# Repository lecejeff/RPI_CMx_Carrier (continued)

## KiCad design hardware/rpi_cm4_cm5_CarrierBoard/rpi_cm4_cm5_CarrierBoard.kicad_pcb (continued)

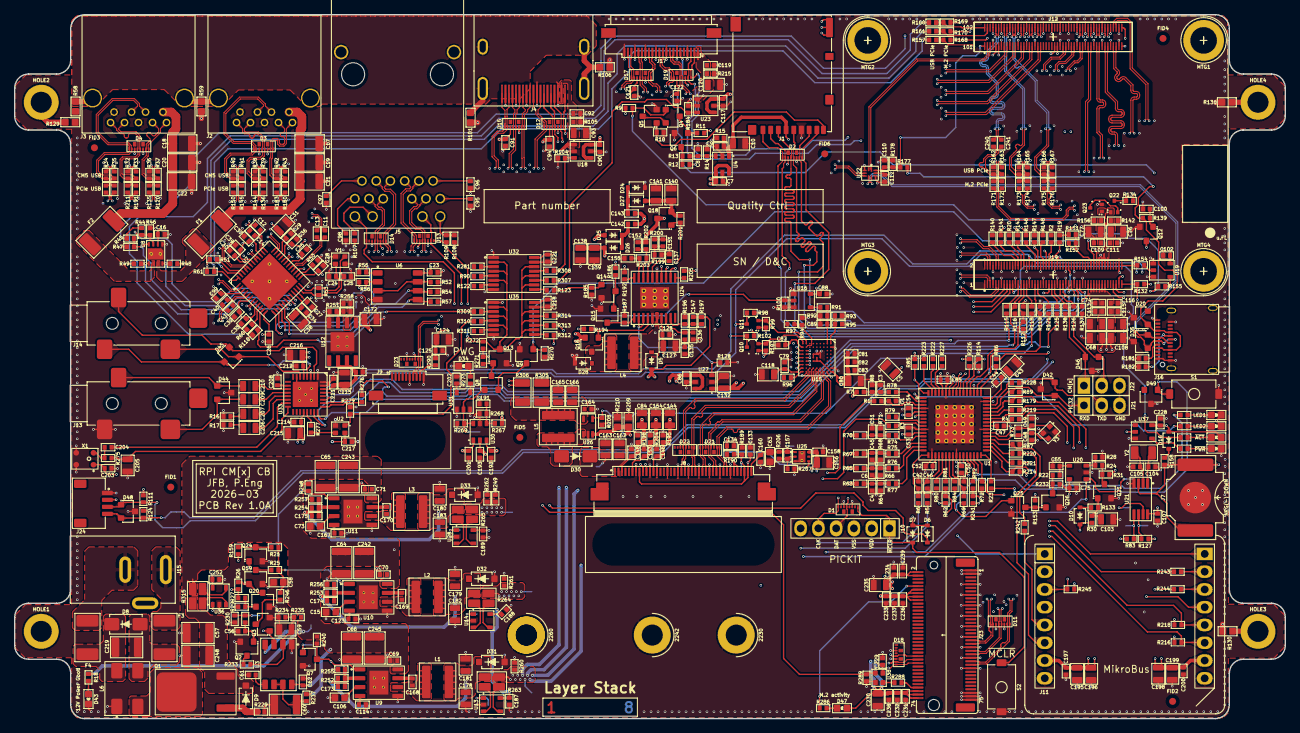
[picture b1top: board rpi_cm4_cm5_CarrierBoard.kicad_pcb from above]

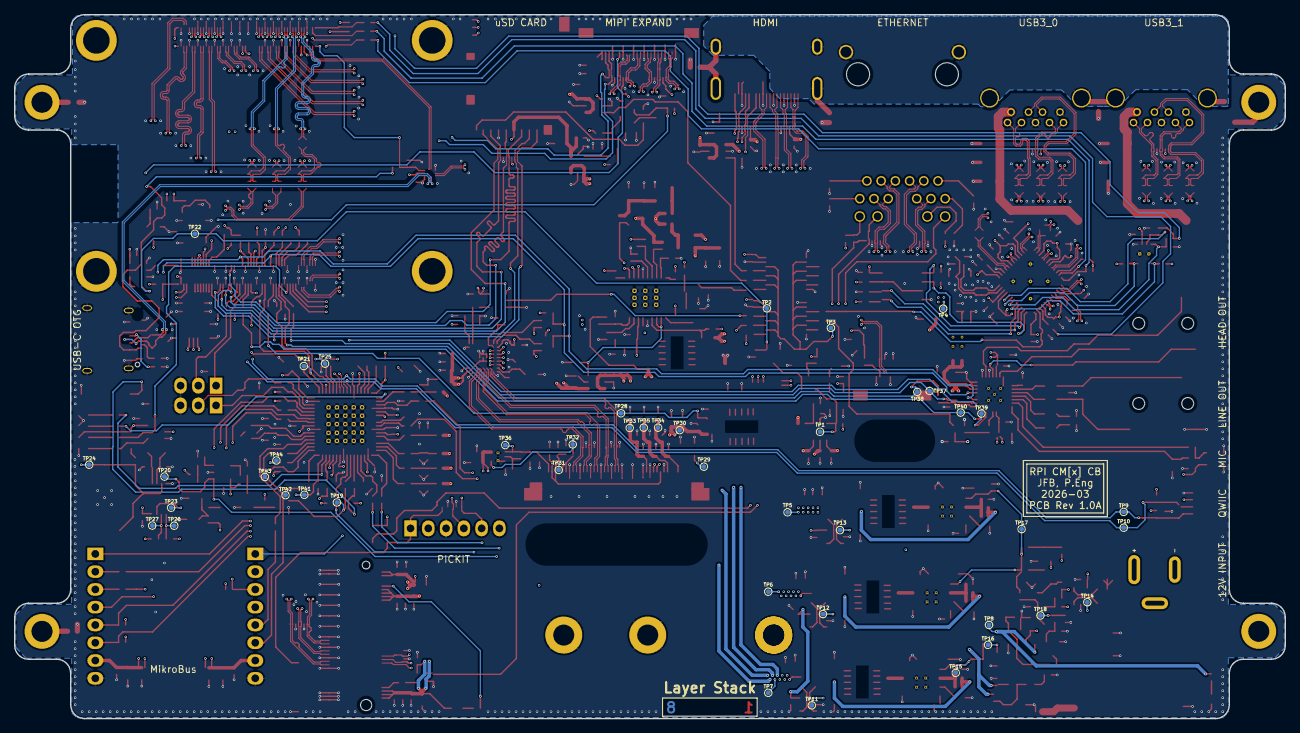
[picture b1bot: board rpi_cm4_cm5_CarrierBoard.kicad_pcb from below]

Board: 8 copper layers, 181.6 x 100.6 mm, 710 parts (45 on the bottom side), 449 nets.

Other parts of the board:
MTG**: Untitled; SLOT_TH_20_5mm
MTG**#2: Untitled; SLOT_TH_5_5mm

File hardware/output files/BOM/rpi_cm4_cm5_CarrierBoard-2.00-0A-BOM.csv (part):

"Reference","Qty","Value","Description","DNP","Exclude from BOM","Exclude from Board","Manufacturer","Manufacturer Part Number","Distributor","Distributor Part Number","Footprint","Datasheet"
"C1,C7,C9,C11,C12,C13,C14,C16,C23,C26,C27,C28,C29,C30,C32,C33,C34,C35,C36,C37,C39,C40,C41,C42,C44,C46,C47,C50,C52,C53,C54,C55,C56,C62,C69,C70,C71,C72,C74,C75,C79,C81,C82,C83,C85,C86,C87,C88,C90,C91,C92,C94,C95,C96,C97,C98,C99,C100,C102,C107,C109,C110,C111,C112,C113,C115,C116,C117,C119,C121,C122,C125,C128,C133,C134,C142,C143,C146,C148,C153,C155,C158,C160,C164,C168,C169,C170,C187,C188,C189,C197,C200,C202,C203,C204,C208,C211,C212,C214,C217,C218,C221,C228,C229,C231,C232,C233,C234,C236,C237,C238,C239,C240,C241,C252,C253","116","0.1u","CAP CER 0.1UF 50V X7R 0402","","","","Murata Electronics","GRM155R71H104KE14D","DigiKey","490-10700-1-ND","footprint:CAP_NONPOL_0402","https://search.murata.co.jp/Ceramy/image/img/A01X/G101/ENG/G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"
"C3,C4,C6,C45,C51,C191,C192,C193,C201","9","1n","CAP CER 1000PF 50V C0G/NP0 0402","","","","Murata Electronics","GRM1555C1H102JA01D","DigiKey","490-3244-1-ND","footprint:CAP_NONPOL_0402","https://search.murata.co.jp/Ceramy/image/img/A01X/G101/ENG/G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"
"C5,C10,C31,C38,C43,C67,C68,C76,C77,C78,C80,C93,C108,C118,C120,C127,C132,C144,C154,C156,C162,C163,C165,C166,C172,C178,C179,C180,C181,C182,C183,C230,C235","33","22u","CAP CER 22UF 25V X5R 0805","","","","Samsung Electro-Mechanics","CL21A226MAYNNNE","DigiKey","1276-CL21A226MAYNNNECT-ND","footprint:CAP_NONPOL_0805","https://mm.digikey.com/Volume0/opasdata/d220001/medias/docus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"
"C8","1","0.1u","CAP CER 0.1UF 50V X7R 0402","DNP","","","Murata Electronics","GRM155R71H104KE14D","DigiKey","490-10700-1-ND","footprint:CAP_NONPOL_0402","https://search.murata.co.jp/Ceramy/image/img/A01X/G101/ENG/G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"
"C15,C58,C63,C73,C106","5","1u","CAP CER 1UF 16V X7R 0603","","","","YAGEO","CC0603KRX7R7BB105","DigiKey","311-1446-1-ND","footprint:CAP_NONPOL_0603","https://www.yageogroup.com/content/datasheet/asset/file/UPY-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"
"C17,C18,C19,C20,C21,C22","6","47u","CAP CER 47UF 16V X5R 1206","","","","TDK Corporation","C3216X5R1C476M160AB","DigiKey","445-6003-1-ND","footprint:CAP_NONPOL_1206","https://product.tdk.com/system/files/dam/doc/product/capacit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"
"C24,C25,C48,C49","4","13p","CAP CER 13PF 50V C0G/NP0 0402","","","","Murata Electronics","GJM1555C1H130GB01D","DigiKey","490-8079-1-ND","footprint:CAP_NONPOL_0402","https://search.murata.co.jp/Ceramy/image/img/A01X/G101/ENG/G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"
"C57,C60,C64,C65,C66,C219,C242,C243,C245,C248","10","10u","CAP CER 10UF 50V X7R 1210","","","","TDK Corporation","C3225X7R1H106K250AC","DigiKey","445-C3225X7R1H106K250ACCT-ND","footprint:CAP_NONPOL_1210","https://product.tdk.com/system/files/dam/doc/product/capacit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"
"C59,C84,C103,C124,C138,C139,C140,C141,C195,C199,C206,C207,C209,C210,C213,C215","16","1u","CAP CER 1UF 50V X7R 0805","","","","YAGEO","CC0805KKX7R9BB105","DigiKey","311-1886-1-ND","footprint:CAP_NONPOL_0805","https://www.yageogroup.com/content/datasheet/asset/file/UPY-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"
"C61,C114,C123,C167","4","10n","CAP CER 10000PF 50V X7R 0402","","","","Murata Electronics","GCM155R71H103KA55D","DigiKey","490-4762-1-ND","footprint:CAP_NONPOL_0402","https://search.murata.co.jp/Ceramy/image/img/A01X/G101/ENG/G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"
"C89","1","1n","CAP CER 1000PF 50V C0G/NP0 0402","DNP","","","Murata Electronics","GRM1555C1H102JA01D","DigiKey","490-3244-1-ND","footprint:CAP_NONPOL_0402","https://search.murata.co.jp/Ceramy/image/img/A01X/G101/ENG/G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"
"C104,C105","2","10p","CAP CER 10PF 50V C0G/NPO 0402","","","","YAGEO","CC0402JRNPO9BN100","DigiKey","311-1014-1-ND","footprint:CAP_NONPOL_0402","https://www.yageo.com/en/Chart/Download/pdf/CC0402JRNPO9BN100"
"C135","1","220p","CAP CER 220PF 50V C0G/NP0 0402","","","","Samsung Electro-Mechanics","CL05C221JB5NNNC","DigiKey","1276-1059-1-ND","footprint:CAP_NONPOL_0402","https://mm.digikey.com/Volume0/opasdata/d220001/medias/docus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"
"C136","1","22p","CAP CER 22PF 50V C0G/NP0 0402","","","","KEMET","C0402C220K5GACTU","DigiKey","399-C0402C220K5GACTUCT-ND","footprint:CAP_NONPOL_0402","https://www.yageogroup.com/content/datasheet/asset/file/KEM_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"
"C137","1","560p","CAP CER 560PF 50V C0G/NP0 0402","","","","Murata Electronics","GRM1555C1H561JA01D","DigiKey","490-3238-1-ND","footprint:CAP_NONPOL_0402","https://search.murata.co.jp/Ceramy/image/img/A01X/G101/ENG/G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"
"C147,C151","2","22p","CAP CER 22PF 50V C0G/NP0 0402","DNP","","","KEMET","C0402C220K5GACTU","DigiKey","399-C0402C220K5GACTUCT-ND","footprint:CAP_NONPOL_0402","https://www.yageogroup.com/content/datasheet/asset/file/KEM_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"
"C152,C157","2","100p","CAP CER 100PF 50V C0G/NPO 0603","","","","YAGEO","CC0603JRNPO9BN101","DigiKey","311-1069-1-ND","footprint:CAP_NONPOL_0402","https://www.yageo.com/en/Chart/Download/pdf/CC0603JRNPO9BN101"
"C173,C174,C175","3","13p","CAP CER 13PF 50V C0G/NP0 0402","DNP","","","Murata Electronics","GJM1555C1H130GB01D","DigiKey","490-8079-1-ND","footprint:CAP_NONPOL_0402","https://search.murata.co.jp/Ceramy/image/img/A01X/G101/ENG/G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"
"C196,C198,C216","3","10u","CAP CER 10UF 16V X5R 0805","","","","Samsung Electro-Mechanics","CL21A106KOQNNNE","DigiKey","1276-1096-1-ND","footprint:CAP_NONPOL_0805","https://mm.digikey.com/Volume0/opasdata/d220001/medias/docus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"
"C205","1","1u","CAP CER 1UF 50V X7R 0805","DNP","","","YAGEO","CC0805KKX7R9BB105","DigiKey","311-1886-1-ND","footprint:CAP_NONPOL_0805","https://www.yageogroup.com/content/datasheet/asset/file/UPY-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"
"D1,D2,D3,D4,D11,D12,D13,D14,D15,D17,D18,D19,D21,D22,D23","15","ESD7016MUTAG","TVS DIODE 5VWM 10VC 8UDFN","","","","onsemi","ESD7016MUTAG","DigiKey","ESD7016MUTAGOSCT-ND","footprint:UDFN8","https://www.onsemi.com/pdf/datasheet/esd7016-d.pdf"
"D5,D6,D7,D10,D16,D24,D25,D26,D27,D28","10","BAT42WS-TP","DIODE SCHOTTKY 30V 100MA SOD323","","","","MCC (Micro Commercial Components)","BAT42WS-TP","DigiKey","BAT42WSTPMSCT-ND","footprint:SOD-323","https://www.mccsemi.com/pdf/Products/BAT42WS-BAT43WS(SOD-323).pdf"
"D8","1","SMAJ12CA","TVS DIODE 12VWM 19.9VC DO214AC","","","","Littelfuse Inc.","SMAJ12CA","DigiKey","SMAJ12CALFCT-ND","footprint:DO-214AC","https://www.littelfuse.com/assetdocs/tvs-diodes-smaj-datashe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"
"D9","1","MMSZ5242B-TP","DIODE ZENER 12V 500MW SOD123","","","","MCC (Micro Commercial Components)","MMSZ5242B-TP","DigiKey","MMSZ5242B-TPMSCT-ND","footprint:SOD-123","https://www.mccsemi.com/pdf/Products/MMSZ5221-MMSZ5267(SOD-123).pdf"
"D20,D35,D42,D44,D45,D46,D48,D49","8","D1213A-02SOL-7","TVS DIODE 3.3VWM 10VC SOT233","","","","Diodes Incorporated","D1213A-02SOL-7","DigiKey","D1213A-02SOL-7DICT-ND","footprint:SOT-23-3","https://www.diodes.com/assets/Datasheets/D1213A_02SOL.pdf"
"D30","1","SK34A-LTP","DIODE SCHOTTKY 40V 3A DO214AC","","","","MCC (Micro Commercial Components)","SK34A-LTP","DigiKey","SK34A-LTPMSCT-ND","footprint:DO-214AC","https://www.mccsemi.com/pdf/Products/SK32A-L-SK310A-L(SMA).pdf"
"D31","1","MMSZ5231B","DIODE ZENER 5.1V 500MW SOD123","","","","Diodes Incorporated","MMSZ5231B-7-F","DigiKey","MMSZ5231B-FDICT-ND","footprint:SOD-123","https://www.diodes.com/assets/Datasheets/ds18010.pdf"
"D32","1","MMSZ5226B","DIODE ZENER 3.3V 500MW SOD123","","","","Diodes Incorporated","MMSZ5226B-7-F","DigiKey","MMSZ5226B-FDICT-ND","footprint:SOD-123","https://www.diodes.com/assets/Datasheets/ds18010.pdf"
"D33","1","DDZ9678-7","DIODE ZENER 1.8V 470MW SOD123","","","","Diodes Incorporated","DDZ9678-7","DigiKey","DDZ9678DICT-ND","footprint:SOD-123","https://www.diodes.com/assets/Datasheets/ds30410.pdf"
"D34,D38,D39,D40,D41,D43,D47","7","LTST-C190KGKT","LED GREEN CLEAR CHIP SMD","","","","Lite-On Inc.","LTST-C190KGKT","DigiKey","160-1435-1-ND","footprint:LED_0603","https://optoelectronics.liteon.com/upload/download/DS22-2000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"
"F1,F2","2","MINISMDC050F-2","PTC RESET FUSE 24V 500MA 1812","","","","Littelfuse Inc.","MINISMDC050F-2","DigiKey","MINISMDC050F-2CT-ND","footprint:PTC_1812","https://www.littelfuse.com/assetdocs/littelfuse-ptc-minismdc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"
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
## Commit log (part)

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2026-01-01 Commit RPI CMx design to Github (initial commit)
2026-01-01 Add dsPIC sheet
2026-01-02 Add power-up and power kill sequences Modify schematics to add net classes for DiffPairs
2026-01-04 Significant update to schematics Add codec, Mikrobus, PIC32A Add power table, design notes for pinmux Add datasheets
2026-01-04 Slight update to hierarchical top sheet
2026-01-04 Preliminary completion of RPI CMx schematics Cleaned up hierarchical root page
2026-01-04 Add power estimation for PCIe NVMe M.2 on 3V3_CB
2026-01-04 Add notes on what software to use to load and edit sequences
2026-01-07 Modify power supply page (input capacitors to buck regulator), update PCB stackup (6-layer JLC 061611-7628 1oz int, 1oz ext, 1.6mm ±10%)
2026-01-09 Add preliminary BOM and preliminary .pdf schmematics Add BOM option for I2C control of ILI2132A for CapTouch HMI Add BOM options and DNP / 0R resistors for CM4 - CM5 build options
2026-01-10 Added power input protection & filter Added dedicated QWIIC connector on RPI CMx I2C6 bus Adjusted power table and PinMux Updated schematics accordingly
2026-01-10 Update watchdog timer circuit to add external watchdog timer IC to be fed by PIC Adjust reset scheme in power supply sheet accordingly Adjust PinMux, regen BOM and PDF schematics (preliminary) Start 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
2026-01-11 Review watchdog timer circuit to prevent race condition during shutdown
2026-01-11 Finished implementation of watchdog circuit All possible reset scenarios documented
2026-01-11 Update BOM + SCH pdf
2026-01-12 Update schematics based on PCB preliminary placement Add preliminary design rules to PCB
2026-01-12 Preliminary design rule
2026-01-12 Update BOM, schematic and preliminary placement
2026-01-13 Update preliminary placement, update DNP, regen BOM + Preliminary schematics
2026-01-18 Update PCB design rules for outer layers differential pairs Update preliminary component placement Update schematics based on PCB placement & remove duplicata / unnecessary components Update design n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
2026-01-23 Document stackup Few changes to schematic based on preliminary PCB placement Update PinMux based on preliminary PCB placement and component positions
2026-01-24 Cosmetic adjustments to schematics
2026-01-25 Significant update in PCB layout; Completed preliminary high speed rules definition and fanout of differential pairs + GND vias. Started routing high speed signals Slight changes to Pinout based on c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
2026-01-31 All differential pairs fanned out, length matched and skew matched, with exception of USB 3.0 (conf. resistors to physical port). Progress on design rules setup.
2026-01-31 Adjust length matching (transmitter vx receiver matching)
2026-02-08 Continue working on the layout. Completed most of power planes planning and pouring Completed all DiffPairs routing and length matching (preliminary)
2026-02-14 Significant update Stackup changed from 6 to 8 layers Changed design notes accordingly Re-routed all differential pairs and length match / skew match Fanout critical signals away from dense areas 95%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
2026-02-15 Add preliminary output files (PCB PDF, Gerbers, IPC-D-356, IPC-2581, Pick_N_Place, etc) Update BOM, SCH PDF Commit PCB design and set to "Review" state
2026-02-15 Cleanup schematic
2026-02-15 Update output files (remove previous rev)
2026-02-15 design review add new rev of output job files
2026-02-16 Modify BOM with DNP for few items
2026-02-16 Update stackup tab with actual layer stack from kicad
2026-02-16 Removed I_1V05; current drawn from 1V05 rail will be reflected through 1V8 rail, as they're connected in cascade
2026-02-17 Update BOM build options (DNP, Exclude from board, etc) Export new BOM and new schematic
2026-02-17 Add test points on relevant signals Re-generate SCH_PDF Re-generate BOM Re-generate all gerbers and relevant PCB output files (still in review phase)
2026-02-17 Add additional datasheets relevant to design
2026-02-17 Push gerbers to repository (review state)
2026-02-18 Correct 3d model for DF40HC connector Correct NPTH hole clearance to zone rule
2026-02-20 Schematic - Add component class for fiducials
    PCB
    - Modify outline to remove 90 degrees angle in board cutout
    - Adjust polygon pour on power plane (add no fill zone under CGND)
    - Adjust soldermask opening for SMT spacers (no soldermask on bottom layer)
    - Adjust rule for fiducial soldermask clearance
    - Adjust polygon rule (remove default clearance, manage by custom rule)
2026-02-20 Schematic review: - Add PD resistor on MAX16928 TFT driver to park TFT_VDD to OFF by default - Adjust DNP fields for PNP and standard BOM PCB review: - Add PD resistor - Adjust few traces, add missin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
2026-02-20 Update BOM and pick N place file following DFM review
2026-02-21 Update PCB based on DFM review - Reduce via size to 0.35 / 0.15mm all around board - Reduce trace width around SN65DSI84
    Continue DFM review and corrections
    Re-generate all output files
2026-02-21 PCB update based on DFM review - Start decreasing trace width to 4mils for DiffPairs routing within ESD protection diodes
2026-02-22 Continue design adjustment following DFM - Adjust all trace width to 4mils next to esd diodes with tight pad to trace spacing - Adjust all vias to 0.2mm drill / 0.35mm pad - Adjust silkscreen - Adjus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
    Still in review
    Regenerate all output files
2026-02-22 Completed preliminary DFM using NextPCB DFM tool Re-generate all output files dated on 2026-02-22 Add 3d step model to output files
2026-02-22 Update 3d step model; remove DNP components and mechanical parts (TFT, RPI CMx, etc)
2026-02-22 Update to KiCad project (step file output options)
2026-02-22 Update SCH_PDF output (add few assembly variant notes, harmonize default cap / res comment on all schematic sheets)
2026-02-22 Update schematic sheets (assembly variants, default cap / res notes)
2026-02-22 Pust update to kicad project file
2026-02-23 Adjust soldermask clearance for slot holes and non-plated through holes Adjust few traces to increase GND planes exposure on all layers
2026-02-25 Update 12MHz oscillator on Audio Codec schematic sheet to solve single source issue and uncommon packaging. Re-generate all output files including schematics and BOM, as well as all PCB output files
2026-02-27 Final commit prior to formal DFM by PCB manufacturer & PCBA Several iterations of DRC checks and validation with CAM software completed Ready for quotation
2026-02-28 Clear ERC markers and cleaned unconnected nets Design freeze
2026-02-28 Re-upload schematic pdf format, unhighlight USB_OTG net
2026-03-01 Add schematicc netlist to git repository
2026-03-01 Adjust pdf schematic output to use "Export --> Plot" function instead of print to pdf. This way, the schematic can be textually parsed and hierarchical structure is maintained and can be easily navig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
2026-03-02 Correct footprint for ENET transceiver (enlarge few holes) Correct SD card (missing 1 retaining pad) Adjust 0402 component
2026-03-02 Kicad prl file update
2026-03-05 Add NextPCB working gerbers
2026-03-07 Add device tree overlays (work in progress) for CM4 and CM5 platforms
2026-03-08 Add config.txt files for RPI CM4 and CM5 variant. Subject to frequent change moving forward with bringup
2026-03-08 Remove overlays for common folder, move then to CM4 and CM5 folders (device dependent overlays)
2026-03-08 Add overlays in device specific folder
2026-03-08 Adjust device tree overlays based on hardware-dependent interfaces which varies between CM4 and CM5
2026-03-15 Kicked off DVT test report writing Reviewed power supply design notes & completed data for 3V3 and 5V0 rails Reviewed power-up sequence & adjusted timing based on design freeze data
2026-03-15 forgot to save :(
2026-03-17 Update POWER-ON reset test Add datasheets
2026-03-18 Update DVT report with power kill sequence Update power kill sequence diagram and simulation file
2026-03-28 Prepare DVT design notes
2026-04-04 Update device tree overlays based on actual hardware SGTL5000 I2C mapping based on CM4 and CM5 SGTL5000 I2S mapping based on CM4 and CM5
    Tentative overlay for SN65DSI84
    Update DVT bring-up notes
2026-04-04 change name
2026-04-04 Add working device tree overlay for SN65DSI84 bridge on CM4
2026-04-05 Add firmware_PIC32 project Add prototype tracker Add upd720202 user manual
2026-04-08 Add upd720202 firmware
2026-04-11 Move Rev1_00-0a project + output files to seperate folder
2026-04-11 Add gpio overlay for backlight controller (GPIO 12) prior to completing PWM overlay
2026-05-03 Update DVT for power-up sequence Update prototype tracker with bugs and resolutions found
2026-06-19 Progress in DVT, HW bugs and applicable work item tracker Progress in FW driver development Slight adjustment to config.txt and device tree overlays for CM4 and CM5
2026-06-22 Update power kill and power up sequence following DVT Add PIC32 powerkill validation with pushbutton
2026-06-23 Start power kill sequence qualification
